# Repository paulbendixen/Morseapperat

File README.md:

#Morseapperat
This is a simple morse tranciver, able to communicate over short (~100m) distances  that you can build yourself.

The legality of this relies on a technicality: the actual radio is not what you build, it is just an activator for it.

##Technically
This is just a simple astable multivibrator (jfgi) that will activate the transmitter, and allow the receiver to operate when it is not active.

The transciever set this is built up over is found at: http://www.dx.com/p/433mhz-rf-transmitter-receiver-link-kit-green-221225#.VWtIbeQxWny it is usually used for arduinos or the like.

The whole project is released under CERN Open Hardware 1.2 License

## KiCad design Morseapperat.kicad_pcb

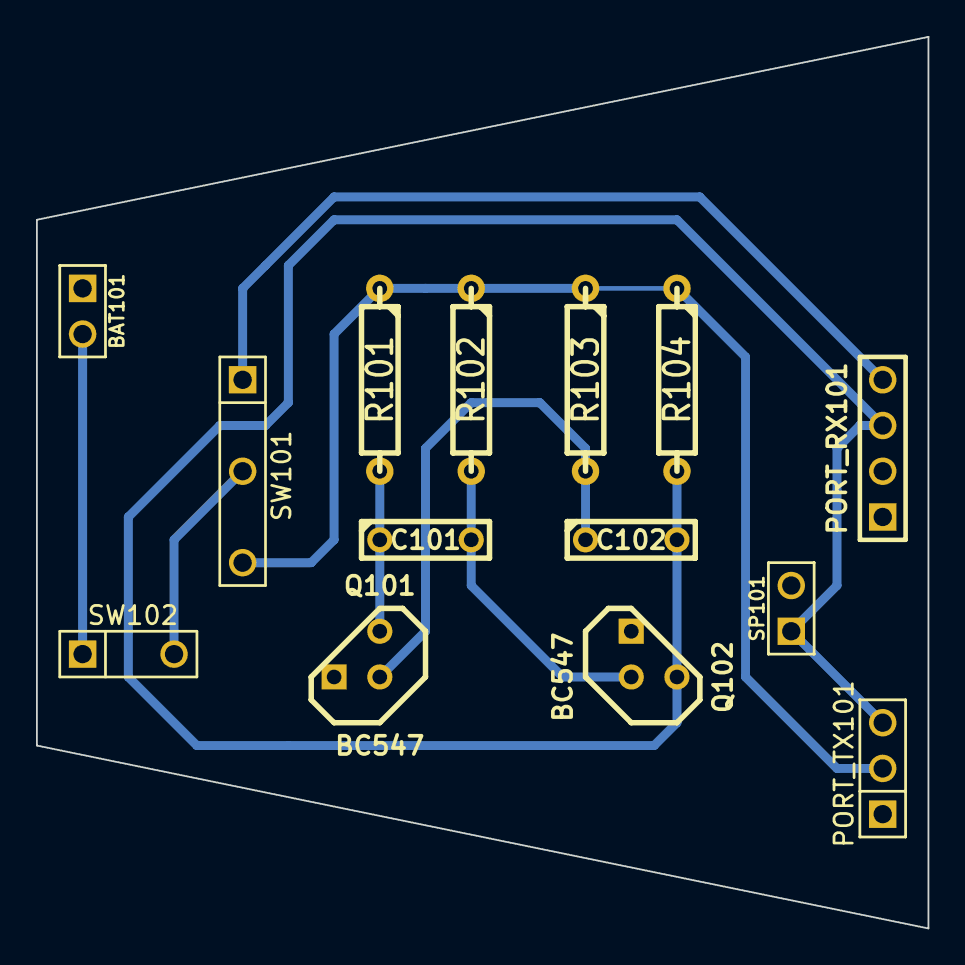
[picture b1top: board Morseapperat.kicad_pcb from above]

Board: 2 copper layers, 49.5 x 49.5 mm, 14 parts (0 on the bottom side), 9 nets.

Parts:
BAT101: CONN_2; PIN_ARRAY_2X1
C101, C102: C; C2
PORT_RX101: RX_CONN; PIN_ARRAY_4x1
PORT_TX101: TX_CONN; PIN_ARRAY_3X1
Q101, Q102: BC547; TO92-123
R101, R102, R103, R104: R; R4
SP101: SPEAKER; PIN_ARRAY_2X1
SW101: DUAL_SWITCH_INV; PIN_ARRAY_3X1_WIDE
SW102: SPST; PIN_ARRAY_2X1_WIDE

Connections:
+BATT: SW101.2, SW102.2
GND: BAT101.1, PORT_RX101.1, PORT_TX101.1, Q101.3, Q102.3, SP101.2
unnamed: PORT_RX101.4, SW101.1
unnamed: BAT101.2, SW102.1
unnamed: C102.2, PORT_RX101.3, PORT_TX101.3, Q102.1, R104.2, SP101.1
unnamed: C101.2, Q102.2, R102.2
unnamed: C102.1, Q101.2, R103.2
unnamed: C101.1, Q101.1, R101.2
unnamed: PORT_TX101.2, R101.1, R102.1, R103.1, R104.1, SW101.3

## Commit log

2015-05-31 First upload
2015-05-31 Added a README.md
2015-05-31 Added an open hardware license
